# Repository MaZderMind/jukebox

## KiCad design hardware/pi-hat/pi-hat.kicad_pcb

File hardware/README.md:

Jukebox Raspberry Pi HAT
========================

This RaspberryPi HAT is an adaptor to connect the old input-panel of my Jukebox (Made in the Germany of the mid 60s) to a modern RasperryPi.
Here is a Twitter-Thread of the complete project: https://twitter.com/mazdermind/status/1204149106270261249

This HAT itself is probably not of any use to anyone else, but it might be of educational use to someone.

Power-System
============

Panel Power Switching
=====================

Panel Input-Protection
======================

GPIO Port Extender
==================

Audio DAC
=========

Hat ID
======

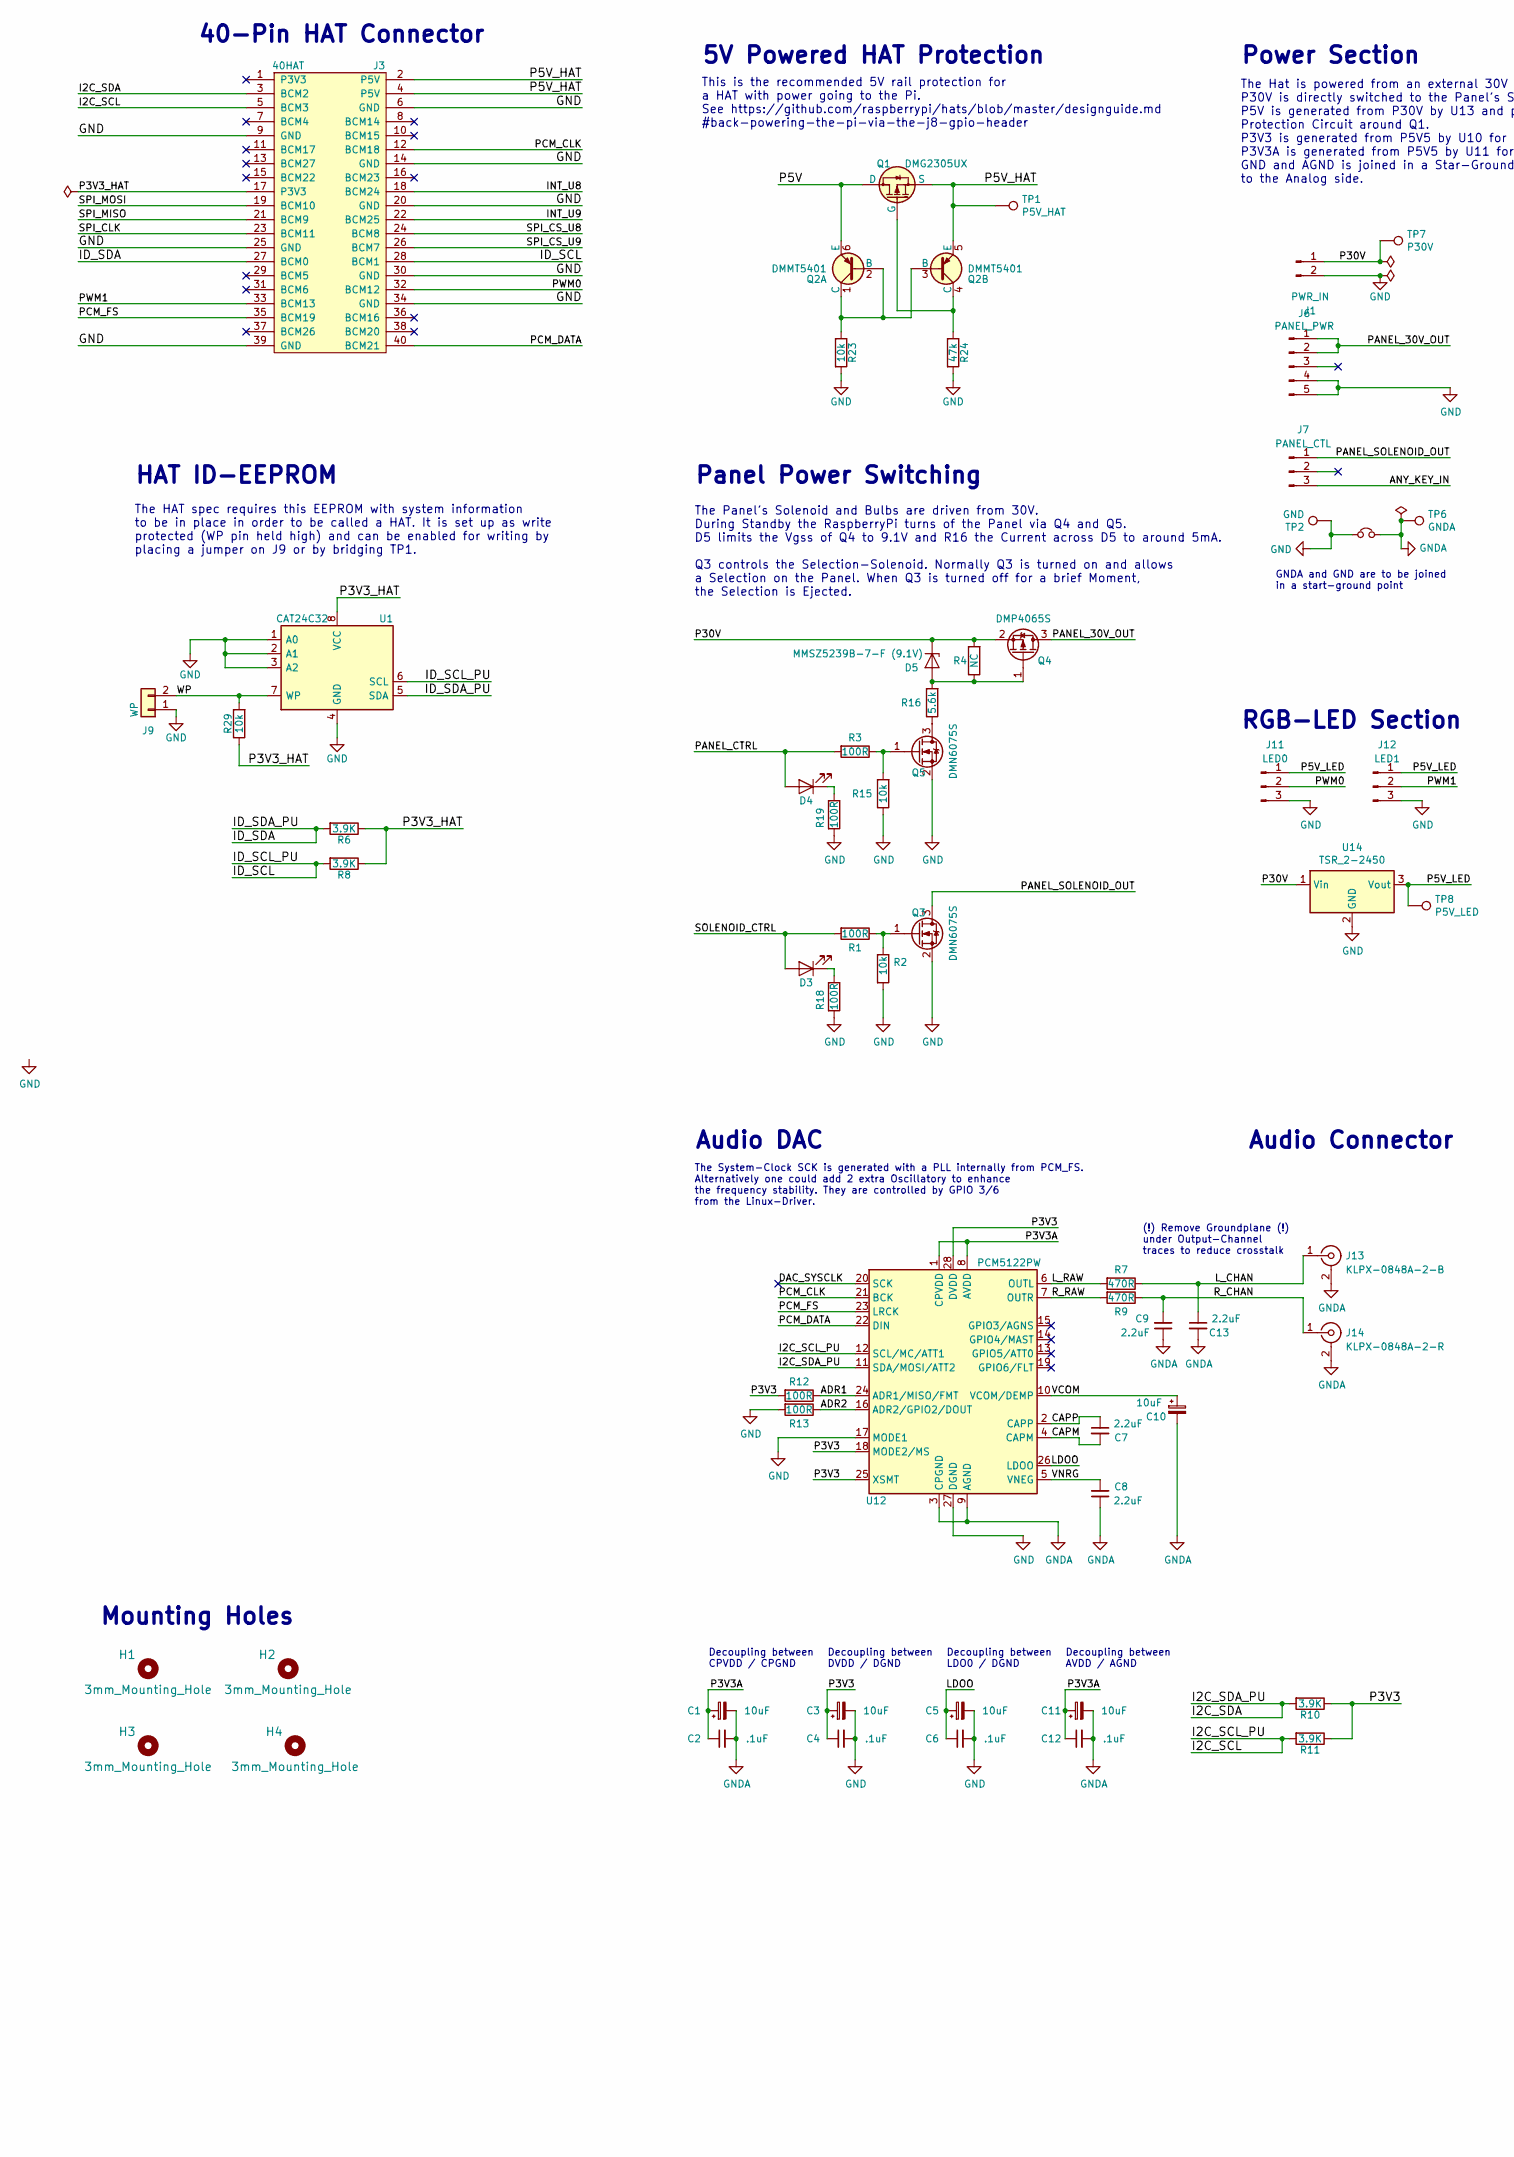
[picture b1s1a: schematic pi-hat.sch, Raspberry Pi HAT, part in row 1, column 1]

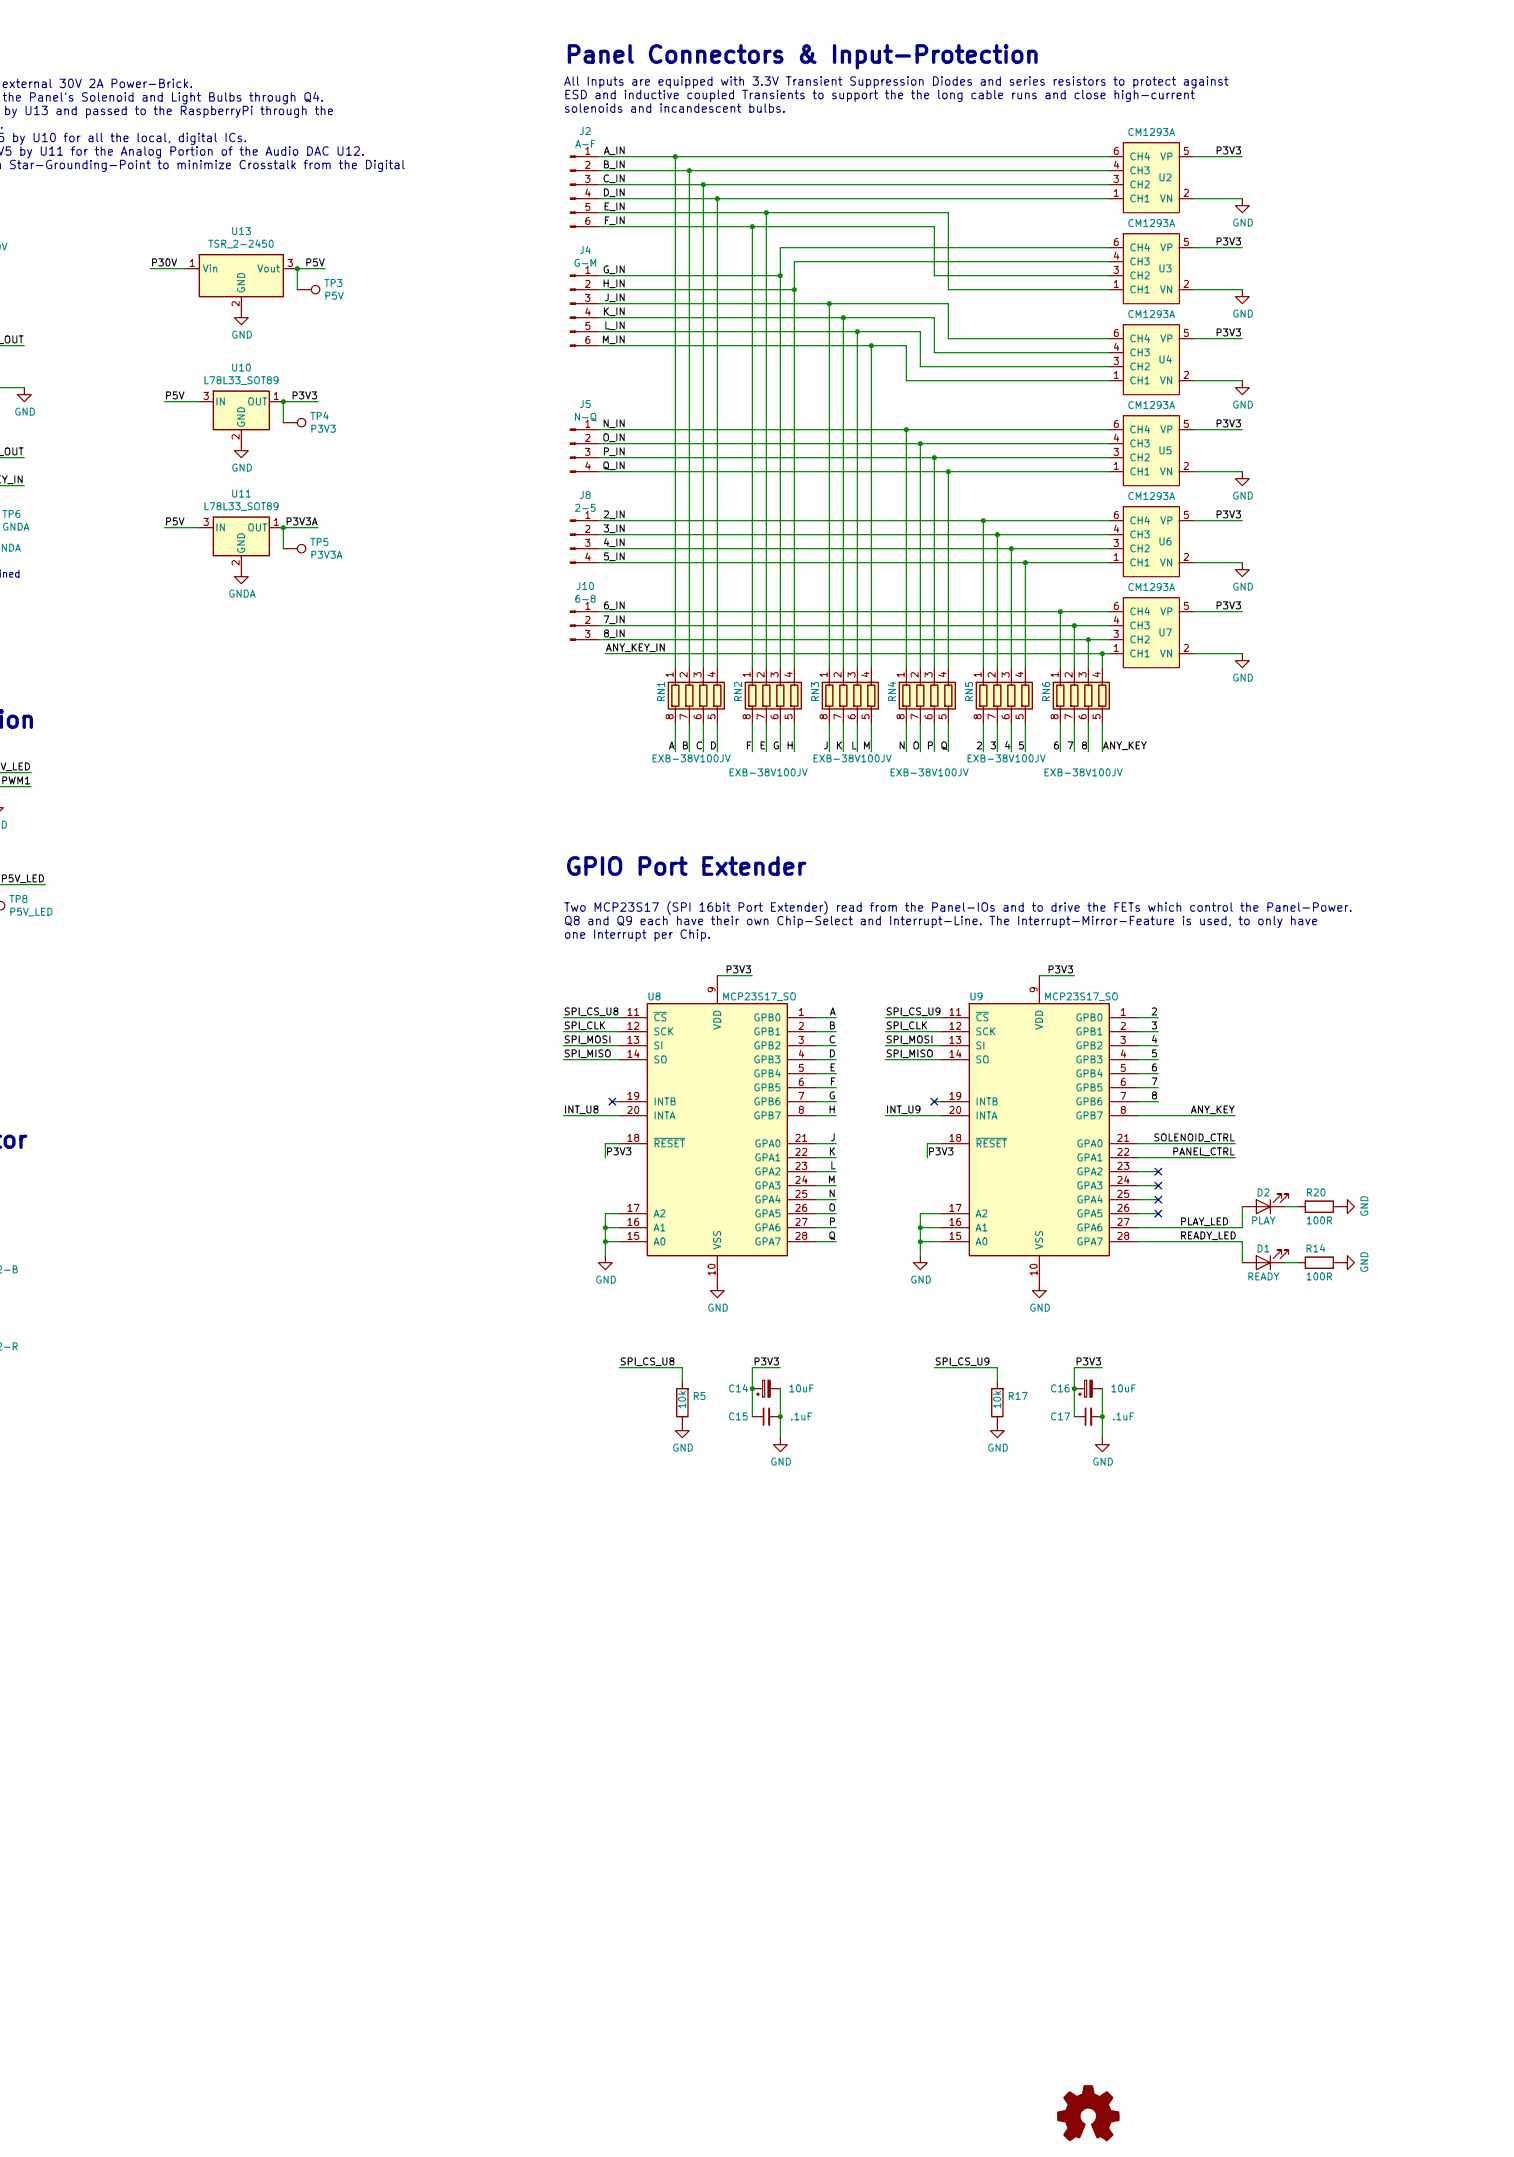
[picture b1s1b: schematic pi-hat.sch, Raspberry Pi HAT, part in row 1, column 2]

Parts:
C1, C3, C5, C10, C11, C14, C16: 10uF; C_0805_2012Metric
C2, C4, C6, C12, C15, C17: .1uF; C_0805_2012Metric
C7, C8, C9, C13: 2.2uF; C_0805_2012Metric
D1: READY; LED_0603_1608Metric
D2: PLAY; LED_0603_1608Metric
D3: SOLENOID; LED_0603_1608Metric
D4: PANEL; LED_0603_1608Metric
D5: MMSZ5239B-7-F (9.1V); D_0805_2012Metric
H1, H2, H3, H4: 3mm_Mounting_Hole; NPTH_3mm_ID
J1: PWR_IN; WUERTH-2-5mm
J2: A-F; JST_XH_B6B-XH-A_1x06_P2.50mm_Vertical
J3: 40HAT; PinSocket_2x20_P2.54mm_Vertical
J4: G-M; JST_XH_B6B-XH-A_1x06_P2.50mm_Vertical
J5: N-Q; JST_XH_B4B-XH-A_1x04_P2.50mm_Vertical
J6: PANEL_PWR; JST_XH_B5B-XH-A_1x05_P2.50mm_Vertical
J7: PANEL_CTL; JST_XH_B3B-XH-A_1x03_P2.50mm_Vertical
J8: 2-5; JST_XH_B4B-XH-A_1x04_P2.50mm_Vertical
J9: WP; PinHeader_1x02_P2.54mm_Vertical
J10: 6-8; JST_XH_B3B-XH-A_1x03_P2.50mm_Vertical
J11: LED0; JST_XH_B3B-XH-A_1x03_P2.50mm_Vertical
J12: LED1; JST_XH_B3B-XH-A_1x03_P2.50mm_Vertical
J13: KLPX-0848A-2-B; KLPX_RCA
J14: KLPX-0848A-2-R; KLPX_RCA
JP1: Jumper_NC_Small; NetTie-2_SMD_Pad0.5mm
OSHW1: Logo_Open_Hardware_Large; OSHW-Logo2_7.3x6mm_SilkScreen
Q1: DMG2305UX; SOT-23
Q2: DMMT5401; SOT-23-6
Q3, Q5: DMN6075S; SOT-23
Q4: DMP4065S; SOT-23
R1, R3, R12, R13, R14, R18, R19, R20: 100R; R_0805_2012Metric
R2, R5, R15, R17, R23, R29: 10k; R_0805_2012Metric
R4: NC; R_0805_2012Metric
R6, R8, R10, R11: 3.9K; R_0805_2012Metric
R7, R9: 470R; R_0805_2012Metric
R16: 5.6k; R_0805_2012Metric
R24: 47k; R_0805_2012Metric
RN1, RN2, RN3, RN4, RN5, RN6: EXB-38V100JV; R_Array_Convex_4x0603
TP1: P5V_HAT; TestPoint_Pad_D1.5mm
TP2: GND; TestPoint_Pad_D1.5mm
TP3: P5V; TestPoint_Pad_D1.5mm
TP4: P3V3; TestPoint_Pad_D1.5mm
TP5: P3V3A; TestPoint_Pad_D1.5mm
TP6: GNDA; TestPoint_Pad_D1.5mm
TP7: P30V; TestPoint_Pad_D1.5mm
TP8: P5V_LED; TestPoint_Pad_D1.5mm
U1: CAT24C32; SOIC-8_3.9x4.9mm_P1.27mm
U2, U3, U4, U5, U6, U7: CM1293A; TSOP-6_1.65x3.05mm_P0.95mm
U8, U9: MCP23S17_SO; SOIC-28W_7.5x17.9mm_P1.27mm
U10, U11: L78L33_SOT89; SOT-89-3
U12: PCM5122PW; TSSOP-28_4.4x9.7mm_P0.65mm
U13, U14: TSR_2-2450; Converter_DCDC_TRACO_TSR-1_THT

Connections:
/2: RN5.8 (R1.2), U9.1 (GPB0)
/2_IN: J8.1, RN5.1 (R1.1), U6.6 (CH4)
/3: RN5.7 (R2.2), U9.2 (GPB1)
/3_IN: J8.2, RN5.2 (R2.1), U6.4 (CH3)
/4: RN5.6 (R3.2), U9.3 (GPB2)
/4_IN: J8.3, RN5.3 (R3.1), U6.3 (CH2)
/5: RN5.5 (R4.2), U9.4 (GPB3)
/5_IN: J8.4, RN5.4 (R4.1), U6.1 (CH1)
/6: RN6.8 (R1.2), U9.5 (GPB4)
/6_IN: J10.1, RN6.1 (R1.1), U7.6 (CH4)
/7: RN6.7 (R2.2), U9.6 (GPB5)
/7_IN: J10.2, RN6.2 (R2.1), U7.4 (CH3)
/8: RN6.6 (R3.2), U9.7 (GPB6)
/8_IN: J10.3, RN6.3 (R3.1), U7.3 (CH2)
/A: RN1.8 (R1.2), U8.1 (GPB0)
/ADR1: R12.1, U12.24 (ADR1/MISO/FMT)
/ADR2: R13.1, U12.16 (ADR2/GPIO2/DOUT)
/ANY_KEY: RN6.5 (R4.2), U9.8 (GPB7)
/ANY_KEY_IN: J7.3, RN6.4 (R4.1), U7.1 (CH1)
/A_IN: J2.1, RN1.1 (R1.1), U2.6 (CH4)
/B: RN1.7 (R2.2), U8.2 (GPB1)
/B_IN: J2.2, RN1.2 (R2.1), U2.4 (CH3)
/C: RN1.6 (R3.2), U8.3 (GPB2)
/CAPM: C7.2, U12.4 (CAPM)
/CAPP: C7.1, U12.2 (CAPP)
/C_IN: J2.3, RN1.3 (R3.1), U2.3 (CH2)
/D: RN1.5 (R4.2), U8.4 (GPB3)
/D_IN: J2.4, RN1.4 (R4.1), U2.1 (CH1)
/E: RN2.7 (R2.2), U8.5 (GPB4)
/E_IN: J2.5, RN2.2 (R2.1), U3.1 (CH1)
/F: RN2.8 (R1.2), U8.6 (GPB5)
/F_IN: J2.6, RN2.1 (R1.1), U3.3 (CH2)
/G: RN2.6 (R3.2), U8.7 (GPB6)
/G_IN: J4.1, RN2.3 (R3.1), U3.6 (CH4)
/H: RN2.5 (R4.2), U8.8 (GPB7)
/H_IN: J4.2, RN2.4 (R4.1), U3.4 (CH3)
/I2C_SCL: J3.5 (BCM3), R11.2, U12.12 (SCL/MC/ATT1)
/I2C_SDA: J3.3 (BCM2), R10.2, U12.11 (SDA/MOSI/ATT2)
/ID_SCL: J3.28 (BCM1), R8.2, U1.6 (SCL)
/ID_SDA: J3.27 (BCM0), R6.2, U1.5 (SDA)
/INT_U8: J3.18 (BCM24), U8.20 (INTA)
/INT_U9: J3.22 (BCM25), U9.20 (INTA)
/J: RN3.8 (R1.2), U8.21 (GPA0)
/J_IN: J4.3, RN3.1 (R1.1), U4.6 (CH4)
/K: RN3.7 (R2.2), U8.22 (GPA1)
/K_IN: J4.4, RN3.2 (R2.1), U4.4 (CH3)
/L: RN3.6 (R3.2), U8.23 (GPA2)
/LDOO: C5.1, C6.1, U12.26 (LDOO)
/L_CHAN: C13.1, J13.1 (In), R7.1
/L_IN: J4.5, RN3.3 (R3.1), U4.3 (CH2)
/L_RAW: R7.2, U12.6 (OUTL)
/M: RN3.5 (R4.2), U8.24 (GPA3)
/M_IN: J4.6, RN3.4 (R4.1), U4.1 (CH1)
/N: RN4.8 (R1.2), U8.25 (GPA4)
/N_IN: J5.1, RN4.1 (R1.1), U5.6 (CH4)
/O: RN4.7 (R2.2), U8.26 (GPA5)
/O_IN: J5.2, RN4.2 (R2.1), U5.4 (CH3)
/P: RN4.6 (R3.2), U8.27 (GPA6)
/P3V3: C3.1, C4.1, C14.1, C15.1, C16.1, C17.1, R10.1, R11.1, R12.2, TP4.1, U2.5 (VP), U3.5 (VP), U4.5 (VP), U5.5 (VP), U6.5 (VP), U7.5 (VP), U8.9 (VDD), U8.18 (~RESET~), U9.9 (VDD), U9.18 (~RESET~), U10.1 (OUT), U12.18 (MODE2/MS), U12.25 (XSMT), U12.28 (DVDD)
/P3V3A: C1.1, C2.1, C11.1, C12.1, TP5.1, U11.1 (OUT), U12.1 (CPVDD), U12.8 (AVDD)
/P3V3_HAT: J3.17 (P3V3), R6.1, R8.1, R29.1, U1.8 (VCC)
/P5V: Q1.3 (D), Q2.6 (E), TP3.1, U10.3 (IN), U11.3 (IN), U13.3 (Vout)
/P5V_HAT: J3.2 (P5V), J3.4 (P5V), Q1.2 (S), Q2.5 (E), TP1.1
/P5V_LED: J11.1, J12.1, TP8.1, U14.3 (Vout)
/P30V: D5.1 (K), J1.1, Q4.2 (S), R4.2, TP7.1, U13.1 (Vin), U14.1 (Vin)
/PANEL_30V_OUT: J6.1, J6.2, Q4.3 (D)
/PANEL_CTRL: D4.2 (A), R3.2, U9.22 (GPA1)
/PANEL_SOLENOID_OUT: J7.1, Q3.3 (D)
/PCM_CLK: J3.12 (BCM18), U12.21 (BCK)
/PCM_DATA: J3.40 (BCM21), U12.22 (DIN)
/PCM_FS: J3.35 (BCM19), U12.23 (LRCK)
/PLAY_LED: D2.2 (A), U9.27 (GPA6)
/PWM0: J3.32 (BCM12), J11.2
/PWM1: J3.33 (BCM13), J12.2
/P_IN: J5.3, RN4.3 (R3.1), U5.3 (CH2)
/Q: RN4.5 (R4.2), U8.28 (GPA7)
/Q_IN: J5.4, RN4.4 (R4.1), U5.1 (CH1)
/READY_LED: D1.2 (A), U9.28 (GPA7)
/R_CHAN: C9.2, J14.1 (In), R9.1
/R_RAW: R9.2, U12.7 (OUTR)
/SOLENOID_CTRL: D3.2 (A), R1.2, U9.21 (GPA0)
/SPI_CLK: J3.23 (BCM11), U8.12 (SCK), U9.12 (SCK)
/SPI_CS_U8: J3.24 (BCM8), R5.2, U8.11 (~CS~)
/SPI_CS_U9: J3.26 (BCM7), R17.2, U9.11 (~CS~)
/SPI_MISO: J3.21 (BCM9), U8.14 (SO), U9.14 (SO)
/SPI_MOSI: J3.19 (BCM10), U8.13 (SI), U9.13 (SI)
/VCOM: C10.1, U12.10 (VCOM/DEMP)
/VNRG: C8.2, U12.5 (VNEG)
/WP: J9.2, R29.2, U1.7 (WP)
GND: C3.2, C4.2, C5.2, C6.2, C14.2, C15.2, C16.2, C17.2, J1.2, J3.6 (GND), J3.9 (GND), J3.14 (GND), J3.20 (GND), J3.25 (GND), J3.30 (GND), J3.34 (GND), J3.39 (GND), J6.4, J6.5, J9.1, J11.3, J12.3, JP1.1, Q3.2 (S), Q5.2 (S), R2.2, R5.1, R13.2, R14.2, R15.1, R17.1, R18.2, R19.2, R20.1, R23.2, R24.2, TP2.1, U1.1 (A0), U1.2 (A1), U1.3 (A2), U1.4 (GND), U2.2 (VN), U3.2 (VN), U4.2 (VN), U5.2 (VN), U6.2 (VN), U7.2 (VN), U8.10 (VSS), U8.15 (A0), U8.16 (A1), U8.17 (A2), U9.10 (VSS), U9.15 (A0), U9.16 (A1), U9.17 (A2), U10.2 (GND), U12.17 (MODE1), U12.27 (DGND), U13.2 (GND), U14.2 (GND)
GNDA: C1.2, C2.2, C8.1, C9.1, C10.2, C11.2, C12.2, C13.2, J13.2 (Ext), J14.2 (Ext), JP1.2, TP6.1, U11.2 (GND), U12.3 (CPGND), U12.9 (AGND)
unnamed: D1.1 (K), R14.1
unnamed: D2.1 (K), R20.2
unnamed: D3.1 (K), R18.1
unnamed: D4.1 (K), R19.1
unnamed: D5.2 (A), Q4.1 (G), R4.1, R16.2
unnamed: Q1.1 (G), Q2.4 (C), R24.1
unnamed: Q2.1 (C), Q2.2 (B), Q2.3 (B), R23.1
unnamed: Q3.1 (G), R1.1, R2.1
unnamed: Q5.1 (G), R3.1, R15.2
unnamed: Q5.3 (D), R16.1

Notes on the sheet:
HAT ID-EEPROM
The HAT spec requires this EEPROM with system information to be in place in order to be called a HAT. It is set up as write protected (WP pin held high) and can be enabled for writing by placing a jumper on J9 or by bridging TP1.
Power Section
The Hat is powered from an external 30V 2A Power-Brick. P30V is directly switched to the Panel's Solenoid and Light Bulbs through Q4. P5V is generated from P30V by U13 and passed to the RaspberryPi through the Protection Circuit around Q1. P3V3 is generated from P5V5 by U10 for all the local, digit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
Mounting Holes
All Inputs are equipped with 3.3V Transient Suppression Diodes and series resistors to protect against ESD and inductive coupled Transients to support the the long cable runs and close high-current solenoids and incandescent bulbs.
Panel Connectors & Input-Protection
Panel Power Switching
Audio Connector
RGB-LED Section
40-Pin HAT Connector
This is the recommended 5V rail protection for a HAT with power going to the Pi. See https://github.com/raspberrypi/hats/blob/master/designguide.md #back-powering-the-pi-via-the-j8-gpio-header
5V Powered HAT Protection
(!) Remove Groundplane (!) under Output-Channel traces to reduce crosstalk
Decoupling between CPVDD / CPGND
Decoupling between DVDD / DGND
Decoupling between LDO0 / DGND
Decoupling between AVDD / AGND
The System-Clock SCK is generated with a PLL internally from PCM_FS. Alternatively one could add 2 extra Oscillatory to enhance the frequency stability. They are controlled by GPIO 3/6 from the Linux-Driver.
Audio DAC
GNDA and GND are to be joined in a start-ground point
GPIO Port Extender
Two MCP23S17 (SPI 16bit Port Extender) read from the Panel-IOs and to drive the FETs which control the Panel-Power. Q8 and Q9 each have their own Chip-Select and Interrupt-Line. The Interrupt-Mirror-Feature is used, to only have one Interrupt per Chip.
The Panel's Solenoid and Bulbs are driven from 30V. During Standby the RaspberryPi turns of the Panel via Q4 and Q5. D5 limits the Vgss of Q4 to 9.1V and R16 the Current across D5 to around 5mA. Q3 controls the Selection-Solenoid. Normally Q3 is turned on and allows a Selection on the Panel. When Q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

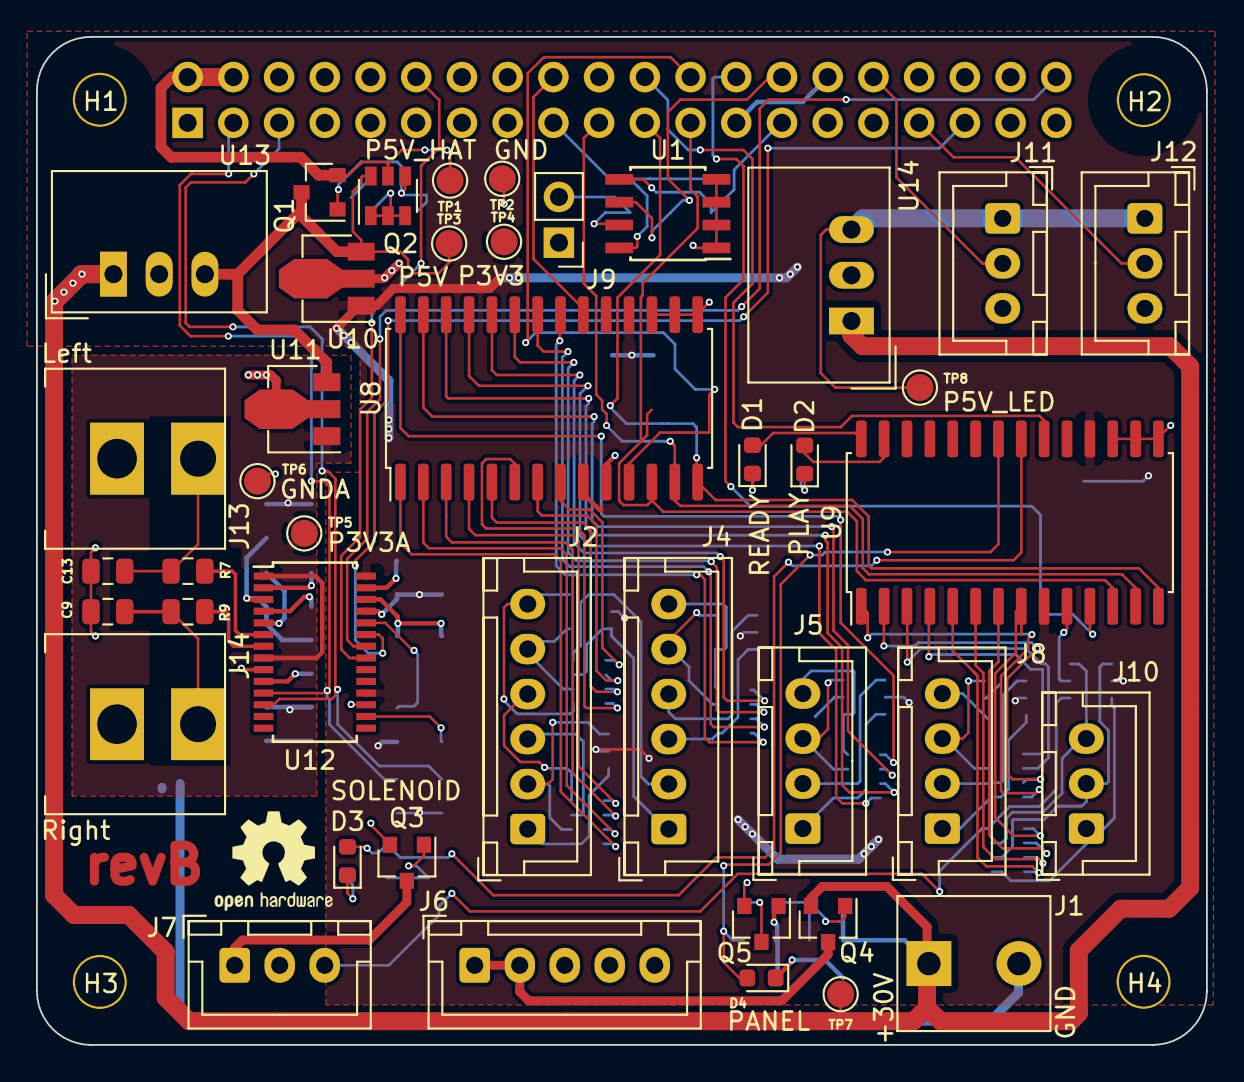
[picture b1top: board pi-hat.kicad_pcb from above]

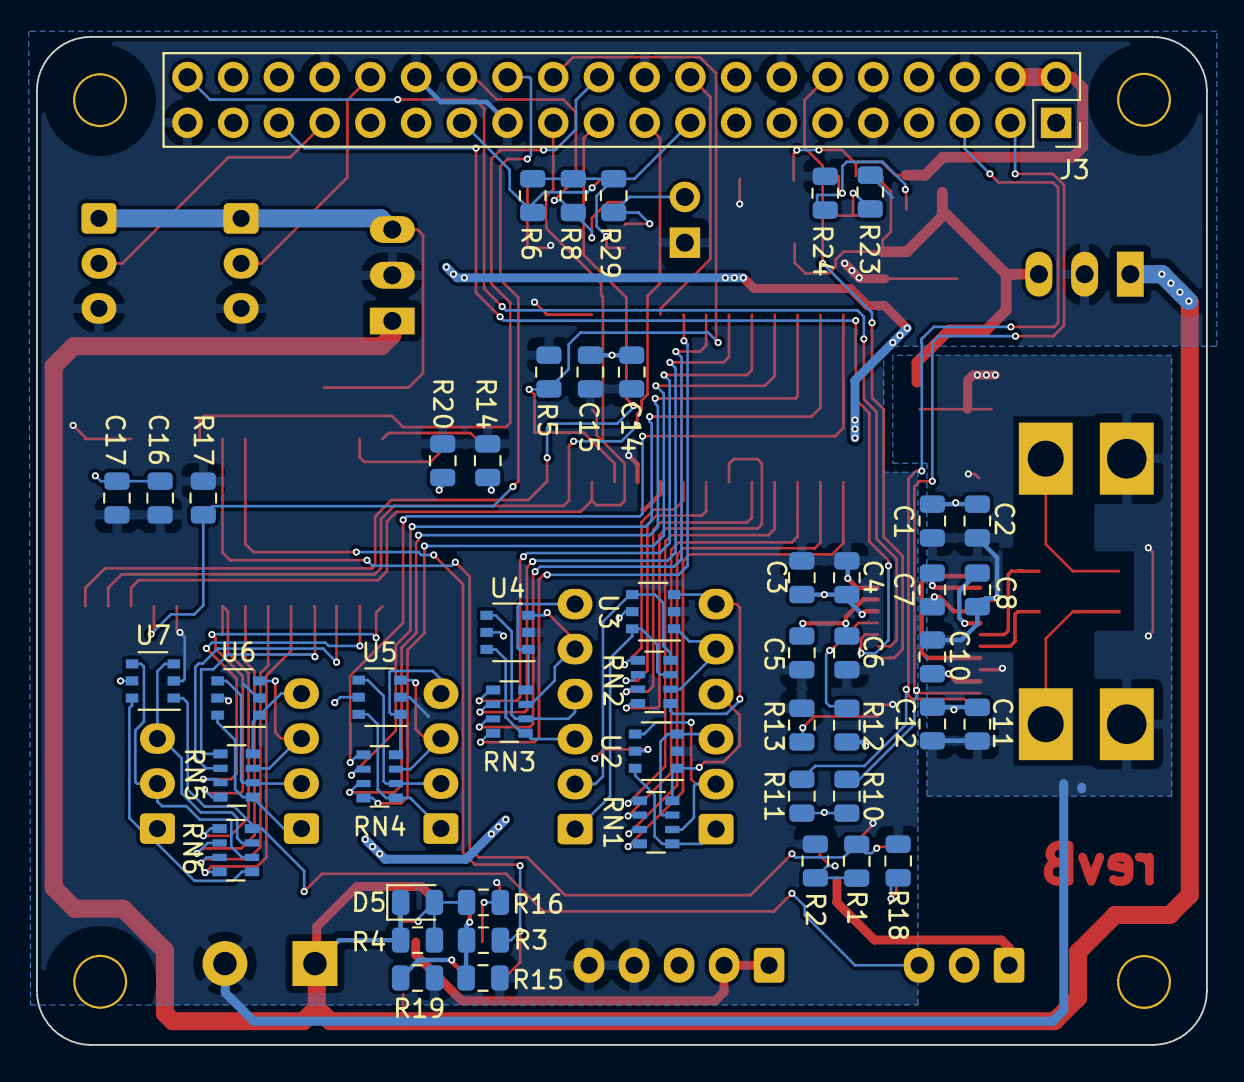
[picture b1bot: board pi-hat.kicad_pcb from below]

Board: 2 copper layers, 65.0 x 56.0 mm, 98 parts (51 on the bottom side), 101 nets.

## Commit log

2019-12-10 initial design
2019-12-14 panel switch fets
2019-12-14 cleanup and documentation
2019-12-14 footprint assignments and early board layout
2019-12-14 remove cache-file from git
2019-12-14 first power traces
2019-12-15 add audio section with split gnd and 3v3
2019-12-15 route io protection
2019-12-15 add pdf schematic
2019-12-15 fully routed
2019-12-17 fiddle with groundplanes and gnd routing
2019-12-17 add icons and voltage testpoints
2019-12-17 add indicator led
2019-12-17 generate gerbers and updated schematic pdf
2019-12-17 add jumper to optionally bridge pcm_clk and sclk as per datasheet
2019-12-17 final cleanup and order
2019-12-17 add 3d renderings
2019-12-21 change topology around Q4
2020-01-01 fix U/9 RESET to P3V3
2020-01-01 split CS between U8/U9, GND Address-Lines, Rename Interrupt-Lines
2020-01-01 fix MISO/MOSI flip
2020-01-01 add LEDs for PLAY, SOLENOID and PANEL Indicaton
2020-01-01 flip E/F
2020-01-01 add TSR-2-2450 local 5V DC/DC converter and 30V Screw-Terminal
2020-01-01 update pdf
2020-01-01 clarify some labels
2020-01-01 upsize paper and enhance schematic layout by using up more space.
2020-01-01 add specific P-Channel FET + Zener
2020-01-01 center GND/AGND join-point
2020-01-02 choose better Q4, D5 and R16; remove R4
2020-01-02 add R4 as NC back
2020-01-02 documentation
2020-01-05 fix line/shield flip on RCA Connectors
2020-01-05 add 5V DC/DC Converter for LED-Strips
2020-01-05 shrink testpoints and sot-6 footprint
2020-01-05 remove sck/fs bridge option
2020-01-05 fix broken gnd, only install a single 5V 2A DC/DC for the LEDs
2020-01-05 re-configure board. route 30V and GND
2020-01-05 route soundcard and 1st gpio extender
2020-01-05 fix drc errors
2020-01-06 fix rca connector pinout
2020-01-07 fix routing
2020-01-07 final routing and silkscreen cleanup
2020-01-07 update 3d and gerbers
2020-01-07 insert correct WUERTH footprint
2020-01-15 initial experiments with the spotify api
2020-01-15 move silkscreen labels
2020-01-15 add more datasheets
2020-01-17 R4 needs to be 10k to discharge the Gate of Q4
2020-01-17 add tsr datasheet
2020-01-18 kernel config
2020-01-20 async software layout
2020-01-20 implement keys handling
2020-01-20 from keys to spotify
2020-01-20 timeout logic
2020-01-20 split jukebox controller and ledstrip-server
2020-01-20 cleanup
2020-01-20 try a much lower timeout
2020-01-20 minimal ledserver connection
2020-01-21 implement simulation of hardware for local development
2020-01-25 give the spotify api some grace time
2020-01-26 implememt no-longer-plying as edge detection
2020-01-26 try to stop playback on exit
2020-01-26 initialize volume to 50%
2020-01-26 remove logging
2020-02-03 ignore pytest cache files
2020-02-03 do not fail with incomplete playback_info
2020-02-03 repair broken requirements.txt
2020-02-08 harden against None-sense
2020-02-08 update actual music collection
2020-02-09 fix line spacing
2020-02-09 fix header height
2020-02-09 document ReverseRepeatIterator
2020-02-09 wip animations
2020-02-09 avoid color skew near the greyscale
2020-02-09 extract colow wipe animations
2020-02-09 simplify calculation by staing in [0:1] right until the end
2020-02-09 convert to pytest
2020-02-09 stars
2020-02-09 extend animation framework
2020-02-09 rate useful animation parameters
2020-02-09 experiment with configuration
2020-02-09 add option to fade between animations
2020-02-09 reorder code
2020-02-09 experiment with external timing control
2020-02-09 meter and solid animation
2020-02-12 nicer interface for sequencing and interrupting
2020-02-12 rename test.py
2020-02-13 pacman
2020-02-13 add restart sequence to pacman
2020-02-13 integrate animations into jukebox code
2020-02-13 start sequence with a fade from black
2020-02-13 interrupt on change
2020-02-13 accept config-path from argv
2020-02-13 allow color codes with #
2020-02-13 start with solid color
2020-02-13 copy changes from prod install
2020-02-13 introduce configured animations
2020-02-13 only relase solenoid when keys are released
2020-02-13 reset current key-combo when invalid
2020-02-13 add systemd service files
2020-02-13 play spotify @100, use alsamixer to lower
2020-02-13 radio support
2020-02-13 add podcast support
2020-02-13 update to spotipy 2.8.0 for autmatic token refresh
2020-02-13 something changed with the labels
2020-02-15 support secondary leds
2020-02-15 configure secondary leds
2020-02-15 in-situ bugfixes
2020-02-19 moar podcasts
2020-02-19 fix secondary leds in-situ
2020-02-19 always terminare ffplay before starting a new one
2020-02-19 use global process pointer
2020-02-19 use the asyncio cancel operation
2020-02-19 do not stop or restart secondary leds if already running
2020-02-22 mixcloud / youtube-dl support
2020-02-22 better error-messages for missing spotify devices
2020-02-22 disable animation before sending the idle frame
2020-02-22 fix calculation of meter leds
2020-02-22 stop running playback before starting a new one
2020-02-23 add mixcloud tracks
2020-02-24 twitter-empfehlungen
2020-02-24 twitter empfehlungen 2
2020-02-24 Rock & Punk Rock
2020-02-29 Swing, Jazz, Blues
2020-02-29 update schematic
2020-02-29 update labels
2020-02-29 configure animations
2020-02-29 fix duplicate key
2020-02-29 fix wrong font
2020-03-29 try to restart raspotify-service when the device vanishes
2020-03-29 reduce logging
2020-03-29 add Samba and Childrens' Music to portfolio
2020-07-31 remove hifiberry parts from dts, use upstream
2020-09-27 remove restart logic and query device only once
2020-09-27 ignore prod config
2021-02-13 add rotary-encoder for volume-control on gpio 14/15
2021-02-13 specify dependencies in Makefile
2021-02-13 simplify name of volume_knob
2021-02-14 implement volume-control
2021-02-14 document dependency on youtube-dl
2021-02-14 simplify code, fix typo
2021-02-26 Bump aiohttp from 3.6.2 to 3.7.4 in /software
    Bumps [aiohttp](https://github.com/aio-libs/aiohttp) from 3.6.2 to 3.7.4.
    - [Release notes](https://github.com/aio-libs/aiohttp/releases)
    - [Changelog](https://github.com/aio-libs/aiohttp/blob/master/CHANGES.rst)
    - [Commits](https://github.com/aio-libs/aiohttp/compare/v3.6.2...v3.7.4)
2021-04-14 setvolume does not automatically unmute the mixer, and when the jukebox client was started with a muted mixer it will re-set the mixer to be muted on every setvolume call
2021-04-20 Bump py from 1.8.1 to 1.10.0 in /software
    Bumps [py](https://github.com/pytest-dev/py) from 1.8.1 to 1.10.0.
    - [Release notes](https://github.com/pytest-dev/py/releases)
    - [Changelog](https://github.com/pytest-dev/py/blob/master/CHANGELOG.rst)
    - [Commits](https://github.com/pytest-dev/py/compare/1.8.1...1.10.0)
2021-04-30 Bump urllib3 from 1.25.7 to 1.25.8 in /software
    Bumps [urllib3](https://github.com/urllib3/urllib3) from 1.25.7 to 1.25.8.
    - [Release notes](https://github.com/urllib3/urllib3/releases)
    - [Changelog](https://github.com/urllib3/urllib3/blob/main/CHANGES.rst)
    - [Commits](https://github.com/urllib3/urllib3/compare/1.25.7...1.25.8)
2021-06-02 Bump urllib3 from 1.25.7 to 1.26.5 in /software
    Bumps [urllib3](https://github.com/urllib3/urllib3) from 1.25.7 to 1.26.5.
    - [Release notes](https://github.com/urllib3/urllib3/releases)
    - [Changelog](https://github.com/urllib3/urllib3/blob/main/CHANGES.rst)
    - [Commits](https://github.com/urllib3/urllib3/compare/1.25.7...1.26.5)
    ---
    updated-dependencies:
2021-07-03 enable dualstack
2021-07-03 don't fail with v4 only devices
2021-07-03 fix typo in comment
2021-07-03 allow transmitting to different strips
2021-07-03 can't get dualstack to work, resort to ipv4 only… grrr…
2021-07-03 remove unused code
2021-07-03 fix formatting
2021-07-18 config readme
2021-07-18 add support for external strips and specific animations made for 1d strips
2021-07-18 update named_animations
2021-07-18 fix static states
2021-07-18 fix sequencer invocation
2021-07-18 fix secondary led sender
2021-07-18 fix example config
2021-07-18 remove prod config, revoked secret
2021-08-19 do not fail, when one of the remote receivers reboot
2021-09-19 update set
2022-12-08 Bump certifi from 2019.11.28 to 2022.12.7 in /software
    Bumps [certifi](https://github.com/certifi/python-certifi) from 2019.11.28 to 2022.12.7.
    - [Release notes](https://github.com/certifi/python-certifi/releases)
    - [Commits](https://github.com/certifi/python-certifi/compare/2019.11.28...2022.12.07)
    ---
    updated-dependencies:
    - dependency-name: certifi
2023-01-23 Bump spotipy from 2.8.0 to 2.22.1 in /software
    Bumps [spotipy](https://github.com/plamere/spotipy) from 2.8.0 to 2.22.1.
    - [Release notes](https://github.com/plamere/spotipy/releases)
    - [Changelog](https://github.com/spotipy-dev/spotipy/blob/master/CHANGELOG.md)
    - [Commits](https://github.com/plamere/spotipy/compare/2.8.0...2.22.1)
    ---
    updated-dependencies:
2024-10-27 Bump idna from 2.8 to 3.7 in /software
    Bumps [idna](https://github.com/kjd/idna) from 2.8 to 3.7.
    - [Release notes](https://github.com/kjd/idna/releases)
    - [Changelog](https://github.com/kjd/idna/blob/master/HISTORY.rst)
    - [Commits](https://github.com/kjd/idna/compare/v2.8...v3.7)
    ---
    updated-dependencies:
2024-10-27 Bump requests from 2.22.0 to 2.32.2 in /software
    Bumps [requests](https://github.com/psf/requests) from 2.22.0 to 2.32.2.
    - [Release notes](https://github.com/psf/requests/releases)
    - [Changelog](https://github.com/psf/requests/blob/main/HISTORY.md)
    - [Commits](https://github.com/psf/requests/compare/v2.22.0...v2.32.2)
    ---
    updated-dependencies:
2024-10-27 Bump zipp from 2.2.0 to 3.19.1 in /software
    Bumps [zipp](https://github.com/jaraco/zipp) from 2.2.0 to 3.19.1.
    - [Release notes](https://github.com/jaraco/zipp/releases)
    - [Changelog](https://github.com/jaraco/zipp/blob/main/NEWS.rst)
    - [Commits](https://github.com/jaraco/zipp/compare/v2.2.0...v3.19.1)
    ---
    updated-dependencies:
2024-10-27 Bump urllib3 from 1.26.5 to 1.26.19 in /software
    Bumps [urllib3](https://github.com/urllib3/urllib3) from 1.26.5 to 1.26.19.
    - [Release notes](https://github.com/urllib3/urllib3/releases)
    - [Changelog](https://github.com/urllib3/urllib3/blob/main/CHANGES.rst)
    - [Commits](https://github.com/urllib3/urllib3/compare/1.26.5...1.26.19)
    ---
    updated-dependencies:
2024-10-27 Bump certifi from 2022.12.7 to 2024.7.4 in /software
    Bumps [certifi](https://github.com/certifi/python-certifi) from 2022.12.7 to 2024.7.4.
    - [Commits](https://github.com/certifi/python-certifi/compare/2022.12.07...2024.07.04)
    ---
    updated-dependencies:
    - dependency-name: certifi
    dependency-type: direct:production
2024-10-27 Bump aiohttp from 3.7.4 to 3.10.2 in /software
    Bumps [aiohttp](https://github.com/aio-libs/aiohttp) from 3.7.4 to 3.10.2.
    - [Release notes](https://github.com/aio-libs/aiohttp/releases)
    - [Changelog](https://github.com/aio-libs/aiohttp/blob/master/CHANGES.rst)
    - [Commits](https://github.com/aio-libs/aiohttp/compare/v3.7.4...v3.10.2)
    ---
    updated-dependencies:
2024-10-27 2024 overhaul
